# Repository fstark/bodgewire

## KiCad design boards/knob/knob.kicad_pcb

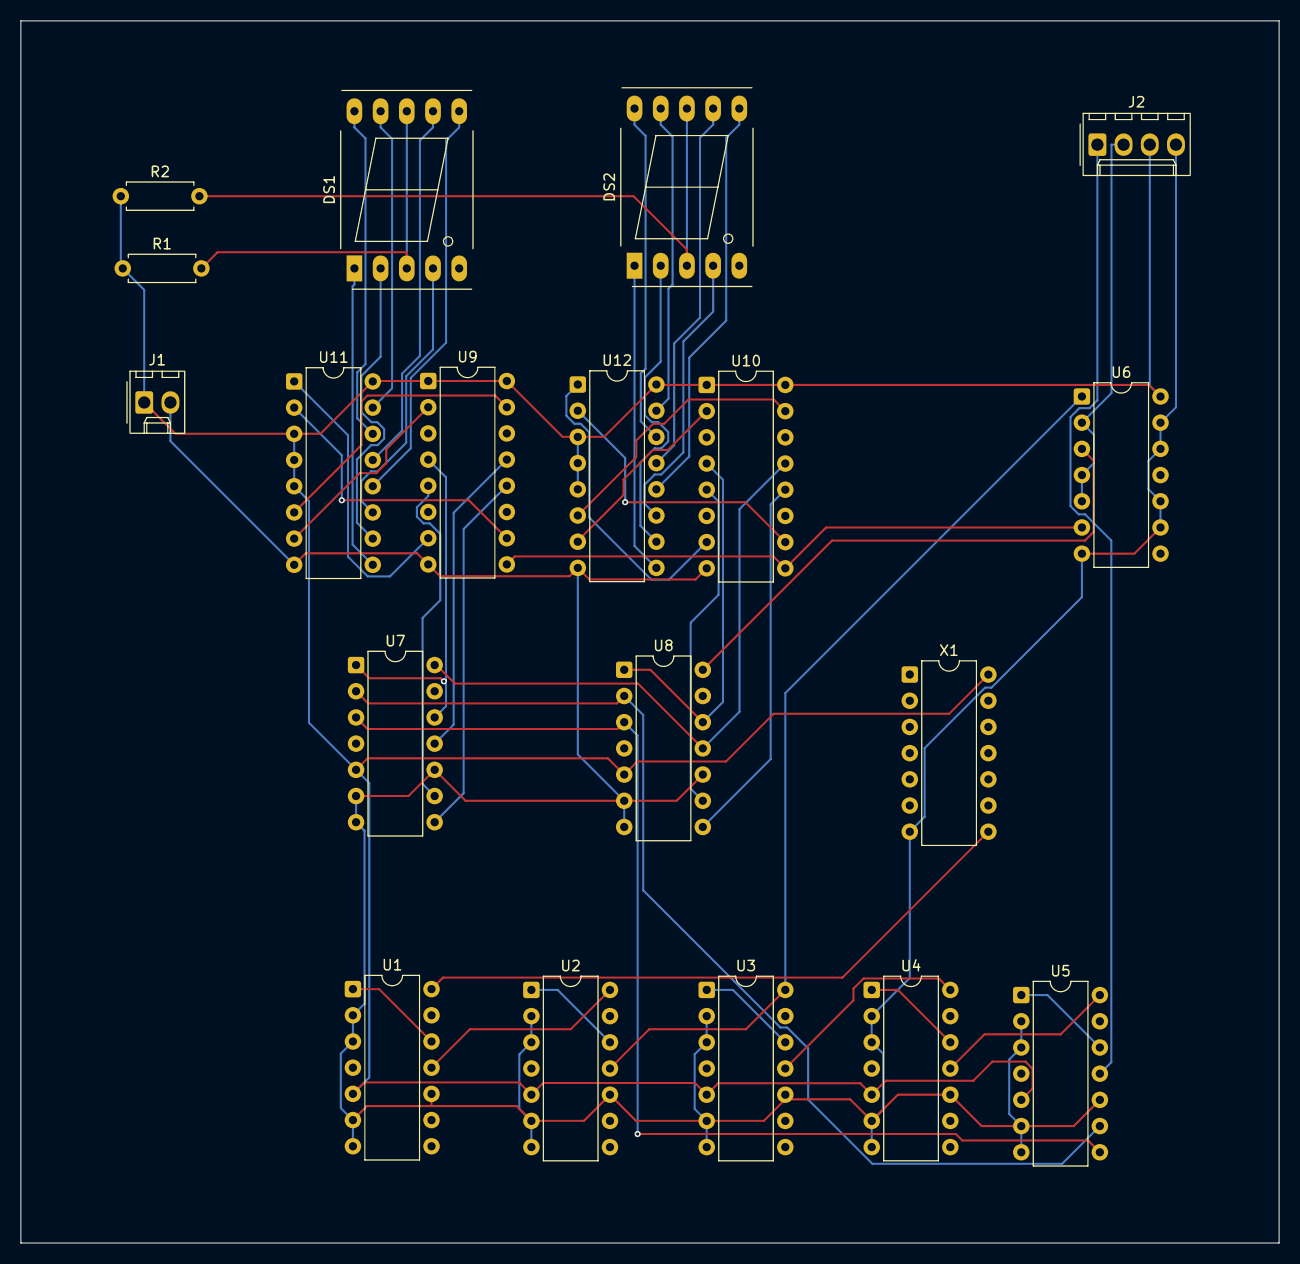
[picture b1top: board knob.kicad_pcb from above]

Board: 2 copper layers, 122.0 x 118.5 mm, 19 parts (0 on the bottom side), 50 nets.

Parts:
DS1, DS2: DIGIT; 7SegmentLED_LTS6760_LTS6780
J1: POWER; Molex_KK-254_AE-6410-02A_1x02_P2.54mm_Vertical
J2: PADDLE; Molex_KK-254_AE-6410-04A_1x04_P2.54mm_Vertical
R1, R2: 330; R_Axial_DIN0207_L6.3mm_D2.5mm_P7.62mm_Horizontal
U1, U2, U3, U4, U5, U7, U8: 74LS90; DIP-14_W7.62mm
U6: 74LS00; DIP-14_W7.62mm
U9, U10: 74LS175; DIP-16_W7.62mm
U11, U12: 74LS47; DIP-16_W7.62mm
X1: OSC; DIP-14_W7.62mm

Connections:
C0: U8.1 (CKB), U8.12 (QA), U10.4 (1D)
C1: U8.9 (QB), U10.5 (2D)
C2: U8.8 (QC), U10.12 (3D)
C3: U7.14 (CKA), U8.11 (QD), U10.13 (4D)
C4: U7.1 (CKB), U7.12 (QA), U9.4 (1D)
C5: U7.9 (QB), U9.5 (2D)
C6: U7.8 (QC), U9.12 (3D)
C7: U7.11 (QD), U9.13 (4D)
CLK: U1.14 (CKA), X1.8 (OUT)
DS1_A: DS1.7 (A), U11.13 (SA_N)
DS1_B: DS1.6 (B), U11.12 (SB_N)
DS1_C: DS1.4 (C), U11.11 (SC_N)
DS1_CA: DS1.3 (CA1), DS1.8 (CA2), R1.2
DS1_D: DS1.2 (D), U11.10 (SD_N)
DS1_E: DS1.1 (E), U11.9 (SE_N)
DS1_F: DS1.9 (F), U11.15 (SF_N)
DS1_G: DS1.10 (G), U11.14 (SG_N)
DS2_A: DS2.7 (A), U12.13 (SA_N)
DS2_B: DS2.6 (B), U12.12 (SB_N)
DS2_C: DS2.4 (C), U12.11 (SC_N)
DS2_CA: DS2.3 (CA1), DS2.8 (CA2), R2.2
DS2_D: DS2.2 (D), U12.10 (SD_N)
DS2_E: DS2.1 (E), U12.9 (SE_N)
DS2_F: DS2.9 (F), U12.15 (SF_N)
DS2_G: DS2.10 (G), U12.14 (SG_N)
F1K: U3.11 (QD), U4.14 (CKA)
F5K: U3.1 (CKB), U3.12 (QA)
F10K: U2.11 (QD), U3.14 (CKA), U6.1 (1A)
F50: U5.1 (CKB), U5.12 (QA)
F50K: U2.1 (CKB), U2.12 (QA)
F100: U4.11 (QD), U5.14 (CKA)
F100K: U1.11 (QD), U2.14 (CKA)
F500: U4.1 (CKB), U4.12 (QA)
F500K: U1.1 (CKB), U1.12 (QA)
GCLK: U6.3 (1Y), U8.14 (CKA)
GND: J1.2 (GND), J2.4 (GND), U1.2 (R01), U1.3 (R02), U1.6 (R91), U1.7 (R92), U1.10 (GND), U2.2 (R01), U2.3 (R02), U2.6 (R91), U2.7 (R92), U2.10 (GND), U3.2 (R01), U3.3 (R02), U3.6 (R91), U3.7 (R92), U3.10 (GND), U4.2 (R01), U4.3 (R02), U4.6 (R91), U4.7 (R92), U4.10 (GND), U5.2 (R01), U5.3 (R02), U5.6 (R91), U5.7 (R92), U5.10 (GND), U6.7 (GND), U6.9 (3A), U6.10 (3B), U6.12 (4A), U6.13 (4B), U7.6 (R91), U7.7 (R92), U7.10 (GND), U8.6 (R91), U8.7 (R92), U8.10 (GND), U9.8 (GND), U10.8 (GND), U11.8 (GND), U12.8 (GND), X1.7 (GND)
L0: U10.2 (1Q), U12.7 (A)
L1: U10.7 (2Q), U12.1 (B)
L2: U10.10 (3Q), U12.2 (C)
L3: U10.15 (4Q), U12.6 (D)
L4: U9.2 (1Q), U11.7 (A)
L5: U9.7 (2Q), U11.1 (B)
L6: U9.10 (3Q), U11.2 (C)
L7: U9.15 (4Q), U11.6 (D)
LATCH: U6.6 (2Y), U9.9 (CLK), U10.9 (CLK)
PULSE: J2.2 (OUT), U6.2 (1B), U6.4 (2A), U6.5 (2B)
TB1: U5.9 (QB), U7.2 (R01), U8.2 (R01)
TB2: U5.8 (QC), U7.3 (R02), U8.3 (R02)
TRIG_N: J2.1 (TRIG_N), U5.11 (QD)
VCC: J1.1 (VCC), J2.3 (VCC), R1.1, R2.1, U1.5 (VCC), U2.5 (VCC), U3.5 (VCC), U4.5 (VCC), U5.5 (VCC), U6.14 (VCC), U7.5 (VCC), U8.5 (VCC), U9.1 (CLR_N), U9.16 (VCC), U10.1 (CLR_N), U10.16 (VCC), U11.3 (LT_N), U11.4 (BI_N), U11.5 (RBI_N), U11.16 (VCC), U12.3 (LT_N), U12.4 (BI_N), U12.5 (RBI_N), U12.16 (VCC), X1.14 (VCC)

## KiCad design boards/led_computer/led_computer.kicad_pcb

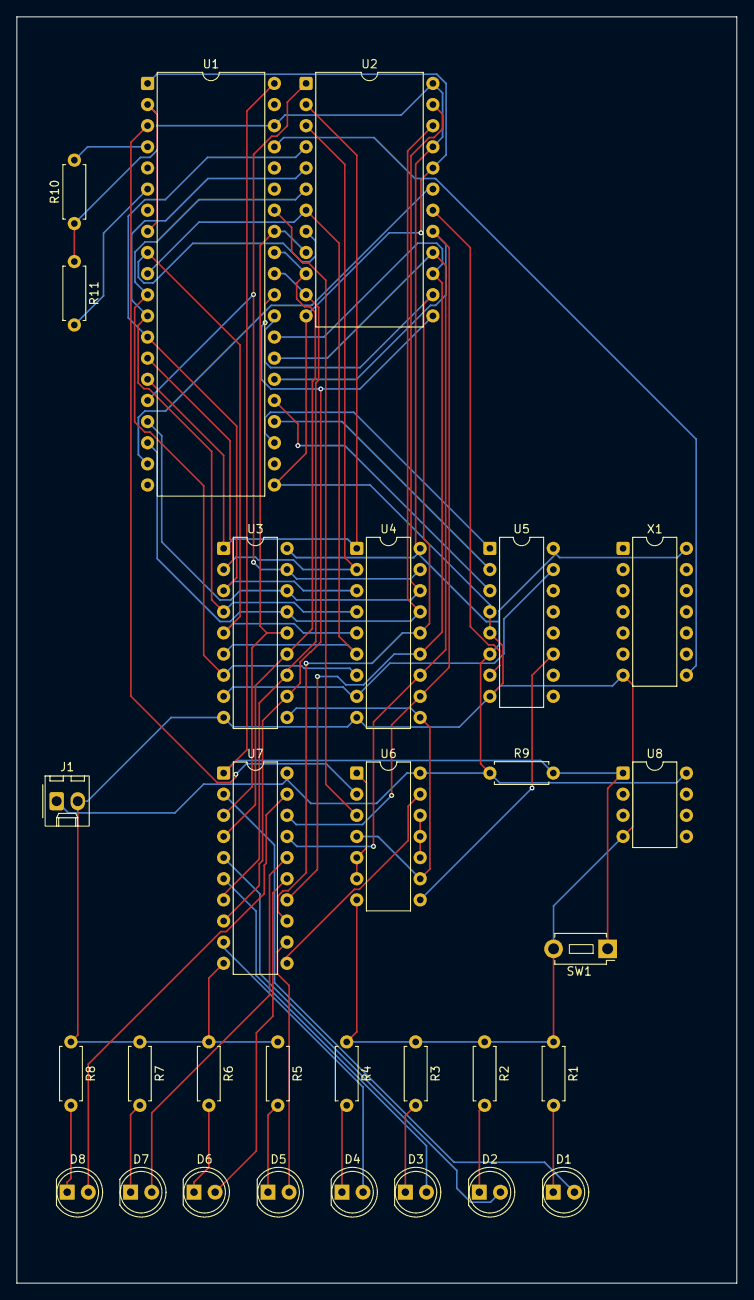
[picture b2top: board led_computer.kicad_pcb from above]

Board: 2 copper layers, 86.5 x 152.2 mm, 30 parts (0 on the bottom side), 53 nets.

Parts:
D1, D2, D3, D4, D5, D6, D7, D8: LED; LED_D5.0mm
J1: POWER; Molex_KK-254_AE-6410-02A_1x02_P2.54mm_Vertical
R1, R2, R3, R4, R5, R6, R7, R8: 330; R_Axial_DIN0207_L6.3mm_D2.5mm_P7.62mm_Horizontal
R9: 4k7; R_Axial_DIN0207_L6.3mm_D2.5mm_P7.62mm_Horizontal
R10, R11: 3k3; R_Axial_DIN0207_L6.3mm_D2.5mm_P7.62mm_Horizontal
SW1: BUTTON; SW_PUSH_1P1T_6x3.5mm_H5.0_APEM_MJTP1250
U1: 6502; DIP-40_W15.24mm
U2: 2716; DIP-24_W15.24mm
U3, U4: 2114; DIP-18_W7.62mm
U5: 74LS138; DIP-16_W7.62mm
U6: 74LS02; DIP-14_W7.62mm
U7: 74LS273; DIP-20_W7.62mm
U8: POR; DIP-8_W7.62mm
X1: OSC; DIP-14_W7.62mm

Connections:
A0: U1.9 (A0), U2.8 (A0), U3.5 (A0), U4.5 (A0)
A1: U1.10 (A1), U2.7 (A1), U3.6 (A1), U4.6 (A1)
A2: U1.11 (A2), U2.6 (A2), U3.7 (A2), U4.7 (A2)
A3: U1.12 (A3), U2.5 (A3), U3.4 (A3), U4.4 (A3)
A4: U1.13 (A4), U2.4 (A4), U3.3 (A4), U4.3 (A4)
A5: U1.14 (A5), U2.3 (A5), U3.2 (A5), U4.2 (A5)
A6: U1.15 (A6), U2.2 (A6), U3.1 (A6), U4.1 (A6)
A7: U1.16 (A7), U2.1 (A7), U3.17 (A7), U4.17 (A7)
A8: U1.17 (A8), U2.23 (A8), U3.16 (A8), U4.16 (A8)
A9: U1.18 (A9), U2.22 (A9), U3.15 (A9), U4.15 (A9)
A10: U1.19 (A10), U2.19 (A10)
A13: U1.23 (A13), U5.1 (A)
A14: U1.24 (A14), U5.2 (B)
A15: U1.25 (A15), U5.3 (C)
DB0: U1.33 (D0), U2.9 (O0), U3.14 (IO1), U7.3 (1D)
DB1: U1.32 (D1), U2.10 (O1), U3.13 (IO2), U7.4 (2D)
DB2: U1.31 (D2), U2.11 (O2), U3.12 (IO3), U7.7 (3D)
DB3: U1.30 (D3), U2.13 (O3), U3.11 (IO4), U7.8 (4D)
DB4: U1.29 (D4), U2.14 (O4), U4.14 (IO1), U7.13 (5D)
DB5: U1.28 (D5), U2.15 (O5), U4.13 (IO2), U7.14 (6D)
DB6: U1.27 (D6), U2.16 (O6), U4.12 (IO3), U7.17 (7D)
DB7: U1.26 (D7), U2.17 (O7), U4.11 (IO4), U7.18 (8D)
GND: J1.2 (GND), R1.1, R2.1, R3.1, R4.1, R5.1, R6.1, R7.1, R8.1, SW1.2, U1.1 (GND), U1.21 (GND2), U2.12 (GND), U2.20 (OE_N), U3.9 (GND), U4.9 (GND), U5.4 (G2A_N), U5.5 (G2B_N), U5.8 (GND), U6.7 (GND), U7.10 (GND), U8.4 (GND), X1.7 (GND)
IRQ_N: R10.2, U1.4 (IRQ_N)
L0: D1.2 (A), U7.2 (1Q)
L1: D2.2 (A), U7.5 (2Q)
L2: D3.2 (A), U7.6 (3Q)
L3: D4.2 (A), U7.9 (4Q)
L4: D5.2 (A), U7.12 (5Q)
L5: D6.2 (A), U7.15 (6Q)
L6: D7.2 (A), U7.16 (7Q)
L7: D8.2 (A), U7.19 (8Q)
LATCH_CLK: U6.13 (4Y), U7.11 (CLK)
LATCH_N: U5.11 (Y4_N), U6.8 (3A)
LATCH_WR: U6.10 (3Y), U6.11 (4A), U6.12 (4B)
LK0: D1.1 (K), R1.2
LK1: D2.1 (K), R2.2
LK2: D3.1 (K), R3.2
LK3: D4.1 (K), R4.2
LK4: D5.1 (K), R5.2
LK5: D6.1 (K), R6.2
LK6: D7.1 (K), R7.2
LK7: D8.1 (K), R8.2
NMI_N: R11.2, U1.6 (NMI_N)
PHI0: U1.37 (PHI0), X1.8 (OUT)
PHI1: U1.3 (PHI1), U6.2 (1A)
RAM_N: U3.8 (CS_N), U4.8 (CS_N), U5.15 (Y0_N)
RES_N: R9.2, SW1.1, U1.40 (RES_N), U7.1 (CLR_N), U8.1 (RST_N)
ROM_N: U2.18 (CE_N), U5.7 (Y7_N)
RW: U1.34 (RW), U6.3 (1B)
VCC: J1.1 (VCC), R9.1, R10.1, R11.1, U1.2 (RDY), U1.8 (VCC), U1.38 (SO), U2.21 (VPP), U2.24 (VCC), U3.18 (VCC), U4.18 (VCC), U5.6 (G1), U5.16 (VCC), U6.14 (VCC), U7.20 (VCC), U8.8 (VCC), X1.14 (VCC)
WR: U6.1 (1Y), U6.5 (2A), U6.6 (2B)
WR_N: U3.10 (WE_N), U4.10 (WE_N), U6.4 (2Y), U6.9 (3B)

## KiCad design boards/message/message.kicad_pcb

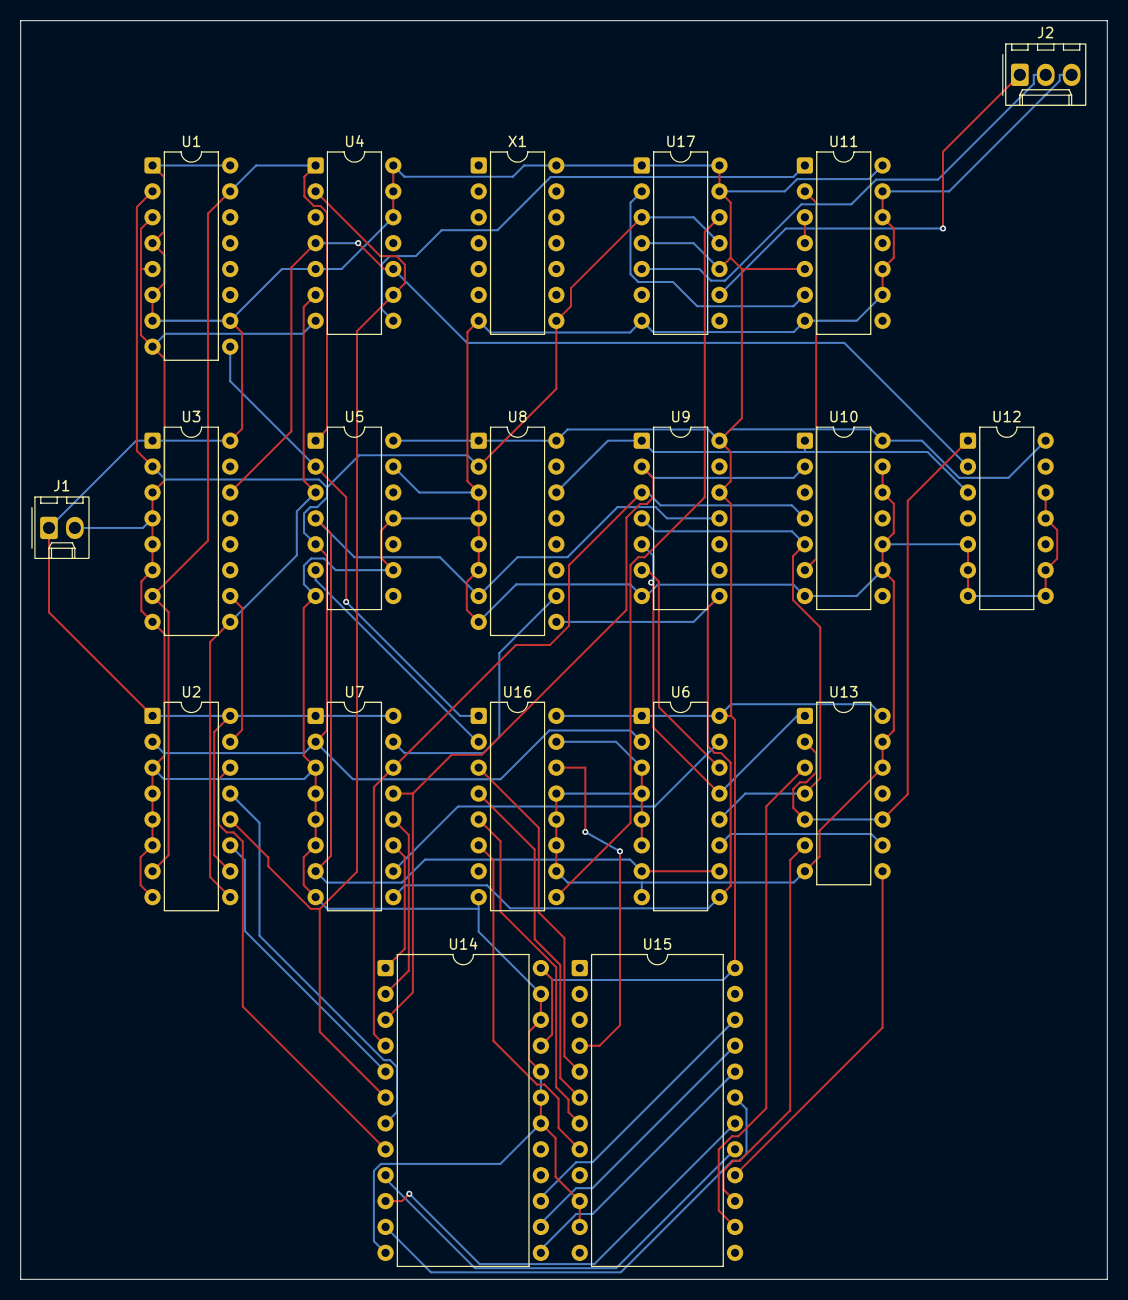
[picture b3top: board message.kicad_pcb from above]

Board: 2 copper layers, 106.6 x 123.5 mm, 20 parts (0 on the bottom side), 48 nets.

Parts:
J1: POWER; Molex_KK-254_AE-6410-02A_1x02_P2.54mm_Vertical
J2: VIDEO; Molex_KK-254_AE-6410-03A_1x03_P2.54mm_Vertical
U1, U2, U3, U6, U7, U8: 74LS161; DIP-16_W7.62mm
U4, U10: 74LS20; DIP-14_W7.62mm
U5: 74LS04; DIP-14_W7.62mm
U9: 74LS30; DIP-14_W7.62mm
U11: 74LS86; DIP-14_W7.62mm
U12: 74LS02; DIP-14_W7.62mm
U13: 74LS08; DIP-14_W7.62mm
U14: 2716; DIP-24_W15.24mm
U15: 2513; DIP-24_W15.24mm
U16: 74LS165; DIP-16_W7.62mm
U17: 74LS74; DIP-14_W7.62mm
X1: OSC; DIP-14_W7.62mm

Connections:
ACTIVE: U12.1 (1Y), U13.2 (1B), U13.5 (2B), U13.10 (3B)
C0: U2.14 (QA), U14.8 (A0)
C1: U2.13 (QB), U14.7 (A1)
C2: U2.12 (QC), U4.2 (1B), U4.9 (2A), U14.6 (A2)
C3: U2.11 (QD), U14.5 (A3)
C4: U3.14 (QA), U4.4 (1C), U4.10 (2B), U12.2 (1A)
CC: U2.15 (RCO), U3.10 (ENT)
CH0: U14.9 (O0), U15.17 (A4)
CH1: U14.10 (O1), U15.18 (A5)
CH2: U14.11 (O2), U15.19 (A6)
CH3: U14.13 (O3), U15.20 (A7)
CH4: U14.14 (O4), U15.21 (A8)
CH5: U14.15 (O5), U15.22 (A9)
CLK: U1.2 (CLK), U2.2 (CLK), U3.2 (CLK), U5.5 (3A), U6.2 (CLK), U7.2 (CLK), U8.2 (CLK), U17.3 (1CLK), U17.11 (2CLK), X1.8 (OUT)
CLK_N: U5.6 (3Y), U16.2 (CLK)
DOT_END: U1.15 (RCO), U2.7 (ENP), U3.7 (ENP), U4.1 (1A), U5.1 (1A)
DOT_LOAD_N: U1.9 (LOAD_N), U5.2 (1Y), U16.1 (SH_LD_N)
F1: U15.4 (O1), U16.14 (D)
F2: U15.5 (O2), U16.3 (E)
F3: U15.6 (O3), U16.4 (F)
F4: U15.7 (O4), U16.5 (G)
F5: U15.8 (O5), U16.6 (H)
FRAME_END_N: U6.9 (LOAD_N), U7.9 (LOAD_N), U8.9 (LOAD_N), U9.8 (Y)
GND: J1.2 (GND), J2.3 (GND), U1.3 (A), U1.5 (C), U1.8 (GND), U2.3 (A), U2.4 (B), U2.5 (C), U2.6 (D), U2.8 (GND), U3.3 (A), U3.4 (B), U3.5 (C), U3.6 (D), U3.8 (GND), U4.7 (GND), U5.7 (GND), U5.9 (4A), U5.11 (5A), U5.13 (6A), U6.3 (A), U6.4 (B), U6.5 (C), U6.6 (D), U6.8 (GND), U7.3 (A), U7.4 (B), U7.5 (C), U7.6 (D), U7.8 (GND), U8.3 (A), U8.4 (B), U8.5 (C), U8.6 (D), U8.8 (GND), U9.7 (GND), U10.7 (GND), U10.9 (2A), U10.10 (2B), U10.12 (2C), U10.13 (2D), U11.7 (GND), U11.9 (3A), U11.10 (3B), U11.12 (4A), U11.13 (4B), U12.5 (2A), U12.6 (2B), U12.7 (GND), U12.8 (3A), U12.9 (3B), U12.11 (4A), U12.12 (4B), U13.7 (GND), U13.12 (4A), U13.13 (4B), U14.12 (GND), U14.18 (CE_N), U14.19 (A10), U14.20 (OE_N), U14.22 (A9), U14.23 (A8), U15.10 (GND), U15.11 (CE_N), U16.8 (GND), U16.10 (SER), U16.11 (A), U16.12 (B), U16.13 (C), U16.15 (CLK_INH), U17.7 (GND), X1.7 (GND)
HSYNC_N: U4.8 (2Y), U11.1 (1A)
LINE_END: U5.4 (2Y), U6.7 (ENP), U6.10 (ENT), U7.7 (ENP), U8.7 (ENP), U9.11 (G)
LINE_END_N: U2.9 (LOAD_N), U3.9 (LOAD_N), U4.6 (1Y), U5.3 (2A)
R1: U13.3 (1Y), U15.14 (A1)
R2: U13.6 (2Y), U15.15 (A2)
R3: U13.8 (3Y), U15.16 (A3)
SYNC: U11.3 (1Y), U11.4 (2A)
SYNC_N: J2.2 (SYNC_N), U17.5 (1Q)
SYNC_N_D: U11.6 (2Y), U17.2 (1D)
V0: U6.14 (QA), U9.6 (F)
V1: U6.13 (QB), U9.5 (E), U13.1 (1A)
V2: U6.12 (QC), U9.4 (D), U10.5 (1D), U13.4 (2A)
V3: U6.11 (QD), U13.9 (3A)
V4: U7.14 (QA), U9.3 (C), U10.4 (1C), U14.4 (A4)
V5: U7.13 (QB), U9.2 (B), U10.2 (1B), U14.3 (A5)
V6: U7.12 (QC), U14.2 (A6)
V7: U7.11 (QD), U14.1 (A7)
V8: U8.14 (QA), U9.1 (A), U10.1 (1A), U12.3 (1B)
VC1: U6.15 (RCO), U7.10 (ENT)
VC2: U7.15 (RCO), U8.10 (ENT)
VCC: J1.1 (VCC), U1.1 (CLR_N), U1.4 (B), U1.6 (D), U1.7 (ENP), U1.10 (ENT), U1.16 (VCC), U2.1 (CLR_N), U2.10 (ENT), U2.16 (VCC), U3.1 (CLR_N), U3.16 (VCC), U4.5 (1D), U4.12 (2C), U4.13 (2D), U4.14 (VCC), U5.14 (VCC), U6.1 (CLR_N), U6.16 (VCC), U7.1 (CLR_N), U7.16 (VCC), U8.1 (CLR_N), U8.16 (VCC), U9.12 (H), U9.14 (VCC), U10.14 (VCC), U11.5 (2B), U11.14 (VCC), U12.14 (VCC), U13.14 (VCC), U14.21 (VPP), U14.24 (VCC), U15.24 (VCC), U16.16 (VCC), U17.1 (1CLR_N), U17.4 (1PRE_N), U17.10 (2PRE_N), U17.13 (2CLR_N), U17.14 (VCC), X1.14 (VCC)
VIDEO: J2.1 (VIDEO), U17.9 (2Q)
VIDEO_D: U16.9 (QH), U17.12 (2D)
VSYNC_N: U10.6 (1Y), U11.2 (1B)

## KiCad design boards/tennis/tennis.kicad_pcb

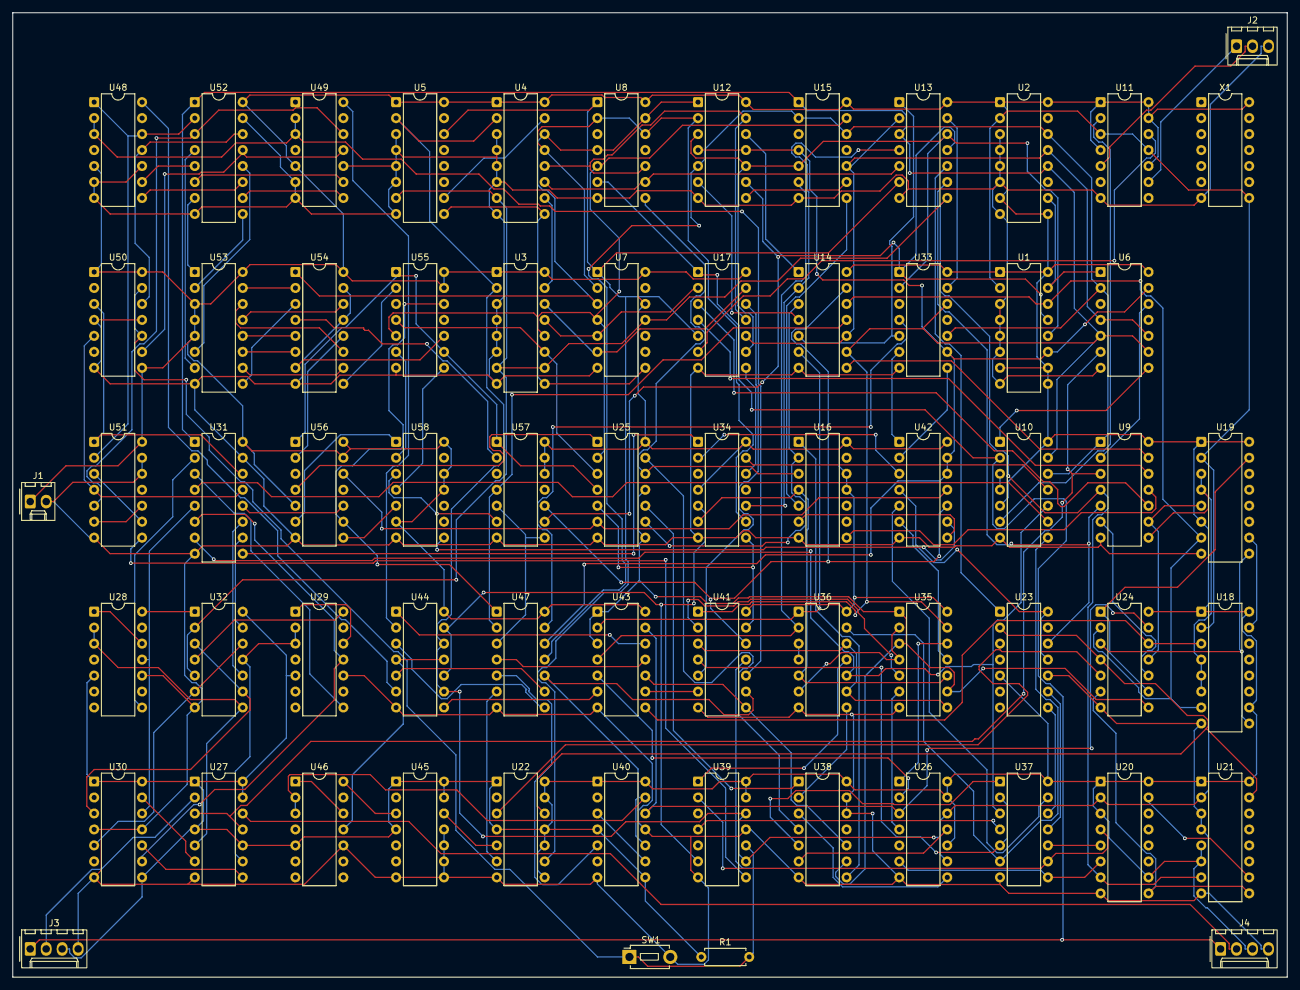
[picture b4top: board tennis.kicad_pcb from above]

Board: 2 copper layers, 202.6 x 153.3 mm, 65 parts (0 on the bottom side), 182 nets.

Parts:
J1: POWER; Molex_KK-254_AE-6410-02A_1x02_P2.54mm_Vertical
J2: VIDEO; Molex_KK-254_AE-6410-03A_1x03_P2.54mm_Vertical
J3, J4: PADDLE; Molex_KK-254_AE-6410-04A_1x04_P2.54mm_Vertical
R1: 1k; R_Axial_DIN0207_L6.3mm_D2.5mm_P7.62mm_Horizontal
SW1: BUTTON; SW_PUSH_1P1T_6x3.5mm_H5.0_APEM_MJTP1250
U1, U2, U3, U4, U5, U18, U19, U20, U21: 74LS161; DIP-16_W7.62mm
U6, U8, U15, U33, U34, U55, U56, U57: 74LS20; DIP-14_W7.62mm
U7, U16, U58: 74LS30; DIP-14_W7.62mm
U9, U41: 74LS04; DIP-14_W7.62mm
U10: 74LS86; DIP-14_W7.62mm
U11, U27: 74LS74; DIP-14_W7.62mm
U12, U17, U35, U43: 74LS27; DIP-14_W7.62mm
U13, U25, U32, U37, U47: 74LS02; DIP-14_W7.62mm
U14, U24, U42, U51: 74LS00; DIP-14_W7.62mm
U22, U26, U30, U39, U40, U44, U45, U50: 74LS107; DIP-14_W7.62mm
U23, U28, U29, U46: 74LS93; DIP-14_W7.62mm
U31, U52, U54: 74LS157; DIP-16_W7.62mm
U36: 74LS08; DIP-14_W7.62mm
U38: 74LS32; DIP-14_W7.62mm
U48, U49: 74LS90; DIP-14_W7.62mm
U53: 74LS48; DIP-16_W7.62mm
X1: OSC; DIP-14_W7.62mm

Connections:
A_TOP: U54.12 (4Y), U56.2 (1B)
BALLV_N: U16.1 (A), U38.8 (3Y)
BALL_CK: U13.10 (3Y), U23.1 (CKB)
BALL_N: U24.8 (3Y), U25.8 (3A), U25.11 (4A), U35.1 (1A), U35.3 (2A), U35.9 (3A), U38.9 (3A), U43.1 (1A), U43.3 (2A)
BALL_OFF: U9.5 (3A), U13.9 (3B), U23.12 (QA)
BALL_QB: U23.9 (QB), U37.11 (4A)
BALL_QC: U23.8 (QC), U37.12 (4B)
BALL_QD: U23.11 (QD), U23.14 (CKA), U42.4 (2A)
BC: U54.7 (2Y), U55.10 (2B)
BHC: U18.15 (RCO), U19.10 (ENT)
BOTTOM_N: U8.8 (2Y), U16.3 (C), U25.12 (4B)
BV8: U22.3 (1Q), U23.3 (R02), U24.5 (2B)
BVC: U20.15 (RCO), U21.10 (ENT)
CLK: U1.2 (CLK), U2.2 (CLK), U3.2 (CLK), U4.2 (CLK), U5.2 (CLK), U11.3 (1CLK), U11.11 (2CLK), U18.2 (CLK), U19.2 (CLK), U20.2 (CLK), U21.2 (CLK), U26.9 (2CLK), U26.12 (1CLK), U39.9 (2CLK), U39.12 (1CLK), U44.9 (2CLK), U44.12 (1CLK), X1.8 (OUT)
COL3: U47.1 (1Y), U55.12 (2C), U56.9 (2A)
COL_L_N: U33.6 (1Y), U42.1 (1A)
COL_R_N: U33.8 (2Y), U42.2 (1B)
FAST: U40.5 (2Q), U47.5 (2A)
FE: U54.4 (1Y), U57.2 (1B)
FRAME0: U22.5 (2Q), U45.12 (1CLK)
FRAME0_N: U22.6 (2Q_N), U47.6 (2B)
FRAME1: U45.3 (1Q), U46.14 (CKA)
FRAME_END_N: U3.9 (LOAD_N), U4.9 (LOAD_N), U5.9 (LOAD_N), U7.8 (Y)
GD: U54.9 (3Y), U55.2 (1B)
GLYPH: U42.9 (3A), U58.8 (Y)
GND: J1.2 (GND), J2.3 (GND), J3.4 (GND), J4.4 (GND), SW1.2, U1.3 (A), U1.4 (B), U1.5 (C), U1.6 (D), U1.8 (GND), U2.3 (A), U2.4 (B), U2.5 (C), U2.6 (D), U2.8 (GND), U3.3 (A), U3.4 (B), U3.5 (C), U3.6 (D), U3.8 (GND), U4.3 (A), U4.4 (B), U4.5 (C), U4.6 (D), U4.8 (GND), U5.3 (A), U5.4 (B), U5.5 (C), U5.6 (D), U5.8 (GND), U6.7 (GND), U7.7 (GND), U8.7 (GND), U9.7 (GND), U10.7 (GND), U11.7 (GND), U12.7 (GND), U13.7 (GND), U14.7 (GND), U15.7 (GND), U16.7 (GND), U17.7 (GND), U18.8 (GND), U19.8 (GND), U20.8 (GND), U21.3 (A), U21.4 (B), U21.8 (GND), U22.7 (GND), U23.10 (GND), U24.7 (GND), U25.7 (GND), U26.7 (GND), U27.7 (GND), U28.10 (GND), U29.10 (GND), U30.4 (1K), U30.7 (GND), U30.11 (2K), U31.8 (GND), U31.15 (G_N), U32.7 (GND), U33.7 (GND), U34.7 (GND), U35.7 (GND), U36.7 (GND), U37.7 (GND), U38.7 (GND), U38.12 (4A), U38.13 (4B), U39.7 (GND), U39.11 (2K), U40.7 (GND), U40.11 (2K), U41.7 (GND), U42.7 (GND), U43.7 (GND), U44.7 (GND), U45.7 (GND), U45.8 (2J), U45.9 (2CLK), U45.10 (2CLR_N), U45.11 (2K), U46.10 (GND), U47.7 (GND), U48.6 (R91), U48.7 (R92), U48.10 (GND), U49.6 (R91), U49.7 (R92), U49.10 (GND), U50.4 (1K), U50.7 (GND), U50.11 (2K), U51.7 (GND), U51.12 (4A), U51.13 (4B), U52.8 (GND), U52.15 (G_N), U53.8 (GND), U54.8 (GND), U54.13 (4B), U54.15 (G_N), U55.7 (GND), U56.7 (GND), U57.7 (GND), U58.7 (GND), X1.7 (GND)
GO_DOWN: U26.8 (2J), U38.3 (1Y)
GO_LEFT: U26.4 (1K), U35.6 (2Y)
GO_RIGHT: U26.1 (1J), U35.12 (1Y)
GO_UP: U26.11 (2K), U38.6 (2Y)
H0: U1.14 (QA), U14.12 (4A), U18.7 (ENP), U19.7 (ENP), U24.2 (1B)
H1: U1.13 (QB), U12.9 (3A), U13.11 (4A), U33.1 (1A), U57.9 (2A)
H2: U1.12 (QC), U12.3 (2A), U12.10 (3B), U13.12 (4B), U15.5 (1D), U17.9 (3A), U33.2 (1B)
H3: U1.11 (QD), U6.13 (2D), U12.4 (2B), U12.11 (3C), U15.4 (1C), U33.9 (2A), U42.12 (4A), U42.13 (4B), U47.12 (4B)
H3_N: U25.6 (2B), U42.11 (4Y), U56.12 (2C)
H4: U2.14 (QA), U6.2 (1B), U9.1 (1A), U10.12 (4A), U12.5 (2C), U15.2 (1B), U15.12 (2C), U33.10 (2B), U47.11 (4A)
H4_N: U6.12 (2C), U9.2 (1Y)
H5: U2.13 (QB), U6.4 (1C), U6.10 (2B), U13.2 (1A), U14.10 (3B), U15.10 (2B), U17.10 (3B)
H6: U2.12 (QC), U6.5 (1D), U6.9 (2A), U10.13 (4B), U13.3 (1B), U14.9 (3A), U15.1 (1A), U31.1 (S), U33.12 (2C), U35.13 (1C), U41.1 (1A), U52.1 (S)
H6_N: U35.5 (2C), U41.2 (1Y)
H12_LOW: U13.13 (4Y), U33.13 (2D)
H34_LOW: U33.4 (1C), U47.13 (4Y)
H56_LOW: U13.1 (1Y), U14.5 (2B), U33.5 (1D)
HBALL: U19.15 (RCO), U24.1 (1A), U24.9 (3A)
HBLANK: U9.12 (6Y), U17.4 (2B)
HBLANK_N: U9.13 (6A), U14.8 (3Y)
HC: U1.15 (RCO), U2.10 (ENT), U6.1 (1A)
HDIR: U24.13 (4B), U26.3 (1Q), U40.12 (1CLK), U43.13 (1C)
HDIR_N: U26.2 (1Q_N), U43.5 (2C)
HIT_BOTTOM: U25.13 (4Y), U38.4 (2A)
HIT_HIGH: U37.1 (1Y), U38.5 (2B)
HIT_LOW: U36.8 (3Y), U38.2 (1B)
HIT_TOP: U25.10 (3Y), U38.1 (1A)
HLOAD_N: U18.9 (LOAD_N), U19.9 (LOAD_N), U24.3 (1Y)
HMOVE: U18.3 (A), U24.12 (4A), U43.8 (3Y)
HSYNC_N: U6.8 (2Y), U10.1 (1A)
HX: U10.11 (4Y), U34.13 (2D)
LDONE: U30.3 (1Q), U32.3 (1B), U32.9 (3B)
LEFT_A: U12.6 (2Y), U14.4 (2A)
LEFT_N: U14.6 (2Y), U36.1 (1A), U43.2 (1B)
LINE_END: U3.7 (ENP), U3.10 (ENT), U4.7 (ENP), U5.7 (ENP), U7.11 (G), U9.4 (2Y), U13.8 (3A), U20.7 (ENP), U21.7 (ENP), U32.2 (1A), U32.5 (2A)
LINE_END_N: U6.6 (1Y), U9.3 (2A), U27.3 (1CLK), U27.11 (2CLK)
LOST_LEFT: U44.3 (1Q), U47.8 (3A)
LOST_LEFT_N: U44.2 (1Q_N), U49.14 (CKA)
LOST_RIGHT: U44.5 (2Q), U47.9 (3B)
LOST_RIGHT_N: U44.6 (2Q_N), U48.14 (CKA)
LP0: U28.1 (CKB), U28.12 (QA)
LP2: U28.8 (QC), U31.2 (1A)
LP3: U28.11 (QD), U30.12 (1CLK), U31.5 (2A)
LPADV: U31.11 (3A), U32.10 (3Y)
LPAD_CK: U28.14 (CKA), U32.1 (1Y)
LPULSE: J3.2 (OUT), U27.2 (1D)
LWAIT: U27.5 (1Q), U28.2 (R01), U28.3 (R02), U32.8 (3A)
LWAIT_N: U27.6 (1Q_N), U30.13 (1CLR_N)
MID_A: U37.13 (4Y), U42.5 (2B)
MID_N: U35.11 (3C), U42.6 (2Y)
MISS_LEFT: U43.12 (1Y), U44.1 (1J)
MISS_RIGHT: U43.6 (2Y), U44.8 (2J)
MIX: U9.11 (5A), U16.8 (Y)
MIX_N: U9.10 (5Y), U17.3 (2A)
MOVE: U17.12 (1Y), U41.5 (3A)
MOVE_N: U41.6 (3Y), U43.9 (3A)
MR: U9.8 (4Y), U18.4 (B), U18.5 (C), U18.6 (D), U19.3 (A), U19.4 (B)
MR_N: U9.9 (4A), U19.5 (C), U24.11 (4Y)
NET_A: U12.8 (3Y), U15.9 (2A)
NET_N: U15.8 (2Y), U16.5 (E)
PADV: U31.9 (3Y), U34.1 (1A)
PAD_HIT: U35.8 (3Y), U36.9 (3A), U36.12 (4A), U41.3 (2A)
PAD_HIT_N: U37.2 (1A), U37.5 (2A), U41.4 (2Y)
PAD_N: U16.4 (D), U34.6 (1Y), U35.10 (3B), U36.5 (2B)
PCOL: U34.2 (1B), U42.3 (1Y)
PLAY: U34.5 (1D), U39.6 (2Q_N), U44.10 (2CLR_N), U44.13 (1CLR_N)
QH0_N: U14.11 (4Y), U47.2 (1A), U57.4 (1C)
QH1_N: U47.3 (1B), U57.5 (1D), U57.8 (2Y)
RDONE: U30.5 (2Q), U32.6 (2B), U32.12 (4B)
REGION: U14.13 (4B), U41.12 (6Y), U42.10 (3B), U57.10 (2B)
REGION_N: U25.5 (2A), U34.8 (2Y), U41.13 (6A)
RIGHT_N: U15.6 (1Y), U36.2 (1B), U43.4 (2B)
RP0: U29.1 (CKB), U29.12 (QA)
RP2: U29.8 (QC), U31.3 (1B)
RP3: U29.11 (QD), U30.9 (2CLK), U31.6 (2B)
RPADV: U31.10 (3B), U32.13 (4Y)
RPAD_CK: U29.14 (CKA), U32.4 (2Y)
RPULSE: J4.2 (OUT), U27.12 (2D)
RWAIT: U27.9 (2Q), U29.2 (R01), U29.3 (R02), U32.11 (4A)
RWAIT_N: U27.8 (2Q_N), U30.10 (2CLR_N)
SC0: U52.4 (1Y), U53.7 (A)
SC1: U52.7 (2Y), U53.1 (B)
SC2: U52.9 (3Y), U53.2 (C)
SC3: U52.12 (4Y), U53.6 (D)
SCORE_A: U17.8 (3Y), U34.12 (2C)
SCORE_N: U16.6 (F), U42.8 (3Y)
SEG_A: U53.13 (SA), U54.14 (4A)
SEG_B: U53.12 (SB), U54.5 (2A)
SEG_C: U53.11 (SC), U54.6 (2B)
SEG_D: U53.10 (SD), U54.10 (3B)
SEG_E: U53.9 (SE), U54.3 (1B)
SEG_F: U53.15 (SF), U54.2 (1A)
SEG_G: U53.14 (SG), U54.11 (3A)
SERVE_END: U44.4 (1K), U44.11 (2K), U46.11 (QD)
SERVING: U38.10 (3B), U41.8 (4Y), U43.10 (3B)
SERVING_N: U40.10 (2CLR_N), U40.13 (1CLR_N), U41.9 (4A), U46.2 (R01), U46.3 (R02), U47.10 (3Y)
SET_SHALLOW: U36.11 (4Y), U39.1 (1J)
SET_STEEP: U37.4 (2Y), U39.4 (1K)
SIDES_N: U36.3 (1Y), U36.4 (2A)
SKIP: U43.11 (3C), U47.4 (2Y)
SL0: U48.1 (CKB), U48.12 (QA), U51.2 (1B), U52.2 (1A)
SL1: U48.9 (QB), U52.5 (2A)
SL2: U48.8 (QC), U52.11 (3A)
SL3: U48.11 (QD), U50.12 (1CLK), U52.14 (4A)
SP2: U10.9 (3A), U31.4 (1Y)
SP3: U10.10 (3B), U31.7 (2Y), U36.10 (3B), U37.3 (1B)
SP_MID: U10.8 (3Y), U36.13 (4B), U37.6 (2B)
SR0: U49.1 (CKB), U49.12 (QA), U51.5 (2B), U52.3 (1B)
SR1: U49.9 (QB), U52.6 (2B)
SR2: U49.8 (QC), U52.10 (3B)
SR3: U49.11 (QD), U50.9 (2CLK), U52.13 (4B)
ST0: U46.1 (CKB), U46.12 (QA)
START: U41.10 (5Y), U48.2 (R01), U48.3 (R02), U49.2 (R01), U49.3 (R02)
START_N: R1.2, SW1.1, U39.10 (2CLR_N), U41.11 (5A), U50.10 (2CLR_N), U50.13 (1CLR_N)
STEEP: U20.4 (B), U37.9 (3B), U39.2 (1Q_N)
SYNC: U10.3 (1Y), U10.4 (2A)
SYNC_N: J2.2 (SYNC_N), U11.5 (1Q)
SYNC_N_D: U10.6 (2Y), U11.2 (1D)
T1_N: U56.6 (1Y), U58.1 (A)
T2_N: U55.6 (1Y), U58.2 (B)
T3_N: U57.6 (1Y), U58.3 (C)
T4_N: U55.8 (2Y), U58.4 (D)
T5_N: U56.8 (2Y), U58.5 (E)
TENS: U31.12 (4Y), U56.10 (2B)
TENS_L: U31.14 (4A), U50.3 (1Q), U51.1 (1A)
TENS_R: U31.13 (4B), U50.5 (2Q), U51.4 (2A)
TOP_A: U12.12 (1Y), U14.1 (1A)
TOP_B: U13.4 (2Y), U14.2 (1B), U34.10 (2B)
TOP_N: U14.3 (1Y), U16.2 (B), U25.9 (3B)
TURN_N: U35.2 (1B), U35.4 (2B), U36.6 (2Y)
TURN_ODD: U40.3 (1Q), U40.9 (2CLK)
UNITS: U25.4 (2Y), U55.1 (1A), U55.9 (2A), U56.1 (1A), U57.1 (1A)
V0: U3.14 (QA), U7.6 (F), U17.13 (1C)
V1: U3.13 (QB), U7.5 (E), U17.2 (1B)
V2: U3.12 (QC), U7.4 (D), U8.5 (1D), U15.13 (2D), U25.2 (1A), U55.5 (1D)
V3: U3.11 (QD), U25.3 (1B), U55.4 (1C)
V4: U4.14 (QA), U7.3 (C), U8.4 (1C), U8.13 (2D), U12.1 (1A), U54.1 (S)
V5: U4.13 (QB), U7.2 (B), U8.2 (1B), U8.12 (2C), U12.2 (1B), U34.9 (2A)
V6: U4.12 (QC), U8.10 (2B), U12.13 (1C), U17.11 (3C)
V7: U4.11 (QD), U8.9 (2A), U13.5 (2A)
V8: U5.14 (QA), U7.1 (A), U8.1 (1A), U13.6 (2B), U17.5 (2C), U22.9 (2CLK)
V23_LOW: U25.1 (1Y), U56.4 (1C)
VBALL: U9.6 (3Y), U24.10 (3B)
VC1: U3.15 (RCO), U4.10 (ENT)
VC2: U4.15 (RCO), U5.10 (ENT)
VCC: J1.1 (VCC), J3.3 (VCC), J4.3 (VCC), R1.1, U1.1 (CLR_N), U1.7 (ENP), U1.9 (LOAD_N), U1.10 (ENT), U1.16 (VCC), U2.1 (CLR_N), U2.7 (ENP), U2.9 (LOAD_N), U2.16 (VCC), U3.1 (CLR_N), U3.16 (VCC), U4.1 (CLR_N), U4.16 (VCC), U5.1 (CLR_N), U5.16 (VCC), U6.14 (VCC), U7.12 (H), U7.14 (VCC), U8.14 (VCC), U9.14 (VCC), U10.5 (2B), U10.14 (VCC), U11.1 (1CLR_N), U11.4 (1PRE_N), U11.10 (2PRE_N), U11.13 (2CLR_N), U11.14 (VCC), U12.14 (VCC), U13.14 (VCC), U14.14 (VCC), U15.14 (VCC), U16.11 (G), U16.12 (H), U16.14 (VCC), U17.14 (VCC), U18.1 (CLR_N), U18.10 (ENT), U18.16 (VCC), U19.1 (CLR_N), U19.6 (D), U19.16 (VCC), U20.1 (CLR_N), U20.3 (A), U20.10 (ENT), U20.16 (VCC), U21.1 (CLR_N), U21.5 (C), U21.6 (D), U21.16 (VCC), U22.1 (1J), U22.4 (1K), U22.8 (2J), U22.10 (2CLR_N), U22.11 (2K), U22.13 (1CLR_N), U22.14 (VCC), U23.5 (VCC), U24.14 (VCC), U25.14 (VCC), U26.10 (2CLR_N), U26.13 (1CLR_N), U26.14 (VCC), U27.1 (1CLR_N), U27.4 (1PRE_N), U27.10 (2PRE_N), U27.13 (2CLR_N), U27.14 (VCC), U28.5 (VCC), U29.5 (VCC), U30.1 (1J), U30.8 (2J), U30.14 (VCC), U31.16 (VCC), U32.14 (VCC), U33.14 (VCC), U34.4 (1C), U34.14 (VCC), U35.14 (VCC), U36.14 (VCC), U37.14 (VCC), U38.14 (VCC), U39.13 (1CLR_N), U39.14 (VCC), U40.1 (1J), U40.4 (1K), U40.8 (2J), U40.14 (VCC), U41.14 (VCC), U42.14 (VCC), U43.14 (VCC), U44.14 (VCC), U45.1 (1J), U45.4 (1K), U45.13 (1CLR_N), U45.14 (VCC), U46.5 (VCC), U47.14 (VCC), U48.5 (VCC), U49.5 (VCC), U50.1 (1J), U50.8 (2J), U50.14 (VCC), U51.14 (VCC), U52.16 (VCC), U53.3 (LT_N), U53.4 (BI_N), U53.5 (RBI_N), U53.16 (VCC), U54.16 (VCC), U55.13 (2D), U55.14 (VCC), U56.5 (1D), U56.13 (2D), U56.14 (VCC), U57.12 (2C), U57.13 (2D), U57.14 (VCC), U58.6 (F), U58.11 (G), U58.12 (H), U58.14 (VCC), X1.14 (VCC)
VDIR_N: U20.6 (D), U26.6 (2Q_N), U37.8 (3A)
VIDEO: J2.1 (VIDEO), U11.9 (2Q)
VIDEO_D: U11.12 (2D), U17.6 (2Y)
VLOAD_C: U20.5 (C), U37.10 (3Y)
VLOAD_N: U20.9 (LOAD_N), U21.9 (LOAD_N), U24.6 (2Y)
VRCO: U21.15 (RCO), U22.12 (1CLK), U23.2 (R01), U24.4 (2A)
VSYNC_N: J3.1 (TRIG_N), J4.1 (TRIG_N), U8.6 (1Y), U10.2 (1B), U17.1 (1A)
WIN: U39.8 (2J), U51.8 (3Y)
WIN_L_N: U51.3 (1Y), U51.9 (3A)
WIN_R_N: U51.6 (2Y), U51.10 (3B)

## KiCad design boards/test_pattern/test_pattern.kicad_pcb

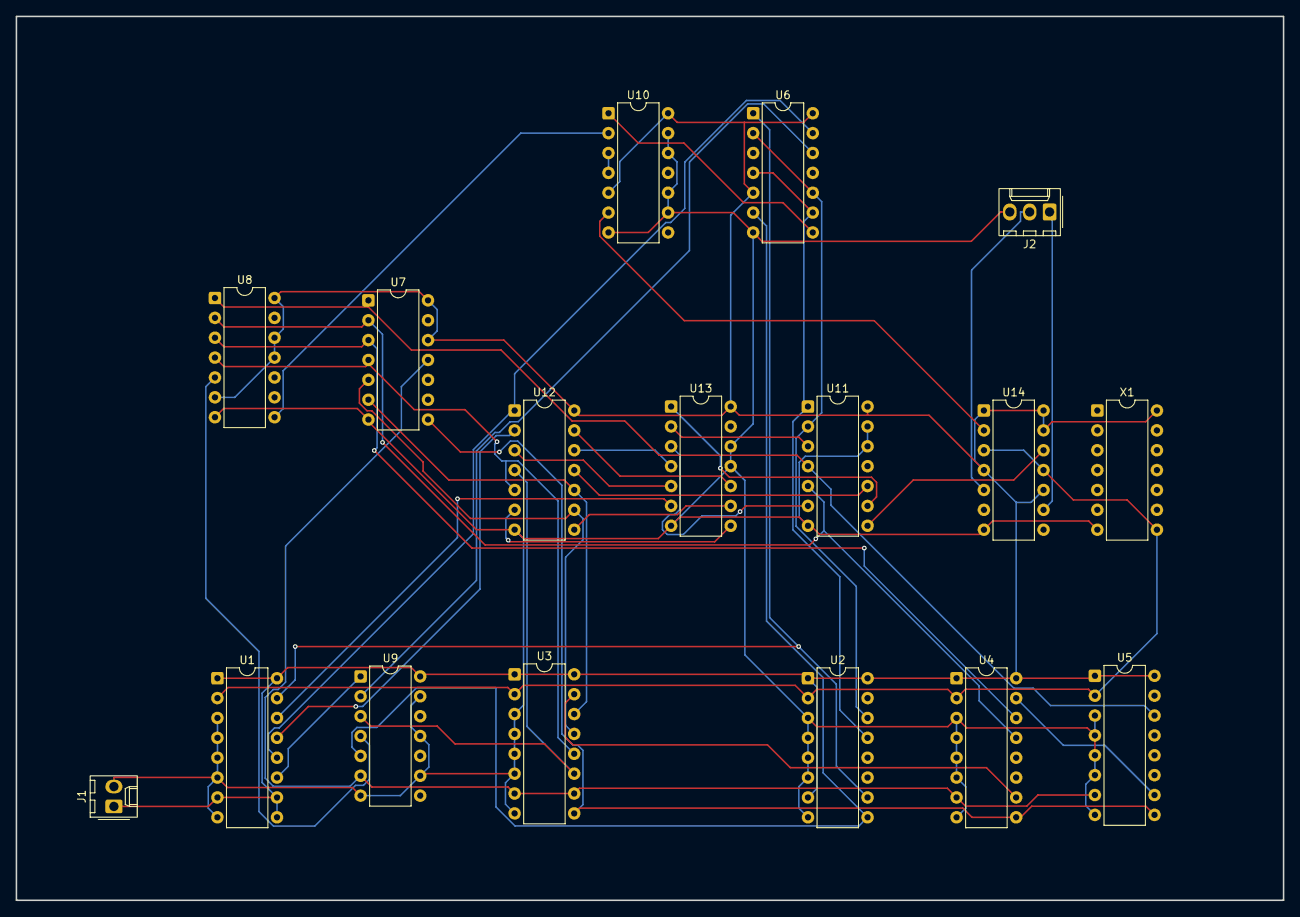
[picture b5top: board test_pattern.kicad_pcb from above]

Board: 2 copper layers, 162.0 x 113.0 mm, 17 parts (0 on the bottom side), 40 nets.

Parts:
J1: POWER; Molex_KK-254_AE-6410-02A_1x02_P2.54mm_Vertical
J2: VIDEO; Molex_KK-254_AE-6410-03A_1x03_P2.54mm_Vertical
U1, U2, U3, U4, U5: 74LS161; DIP-16_W7.62mm
U6: 74LS20; DIP-14_W7.62mm
U7, U8: 74LS30; DIP-14_W7.62mm
U9: 74LS04; DIP-14_W7.62mm
U10: 74LS86; DIP-14_W7.62mm
U11: 74LS08; DIP-14_W7.62mm
U12: 74LS32; DIP-14_W7.62mm
U13: 74LS02; DIP-14_W7.62mm
U14: 74LS74; DIP-14_W7.62mm
X1: OSC; DIP-14_W7.62mm

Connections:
ACTIVE: U11.9 (3A), U13.1 (1Y)
CLK: U1.2 (CLK), U2.2 (CLK), U3.2 (CLK), U4.2 (CLK), U5.2 (CLK), U14.3 (1CLK), U14.11 (2CLK), X1.8 (OUT)
FRAME_END_N: U3.9 (LOAD_N), U4.9 (LOAD_N), U5.9 (LOAD_N), U7.8 (Y)
GND: J1.2 (GND), J2.3 (GND), U1.3 (A), U1.4 (B), U1.5 (C), U1.6 (D), U1.8 (GND), U2.3 (A), U2.4 (B), U2.5 (C), U2.6 (D), U2.8 (GND), U3.3 (A), U3.4 (B), U3.5 (C), U3.6 (D), U3.8 (GND), U4.3 (A), U4.4 (B), U4.5 (C), U4.6 (D), U4.8 (GND), U5.3 (A), U5.4 (B), U5.5 (C), U5.6 (D), U5.8 (GND), U6.7 (GND), U7.7 (GND), U8.7 (GND), U9.7 (GND), U9.9 (4A), U9.11 (5A), U9.13 (6A), U10.7 (GND), U10.9 (3A), U10.10 (3B), U10.12 (4A), U10.13 (4B), U11.7 (GND), U11.12 (4A), U11.13 (4B), U12.7 (GND), U13.7 (GND), U13.11 (4A), U13.12 (4B), U14.7 (GND), X1.7 (GND)
GRID: U11.10 (3B), U12.11 (4Y)
GRIDH: U12.12 (4A), U13.4 (2Y)
GRIDV: U12.13 (4B), U13.10 (3Y)
H0: U1.14 (QA), U13.6 (2B)
H1: U1.13 (QB), U12.2 (1B)
H2: U1.12 (QC), U6.13 (2D), U12.1 (1A)
H3: U1.11 (QD), U9.1 (1A)
H3_N: U6.12 (2C), U9.2 (1Y)
H4: U2.14 (QA), U6.2 (1B), U6.10 (2B), U11.2 (1B)
H5: U2.13 (QB), U6.4 (1C), U6.9 (2A), U11.1 (1A)
H21: U12.3 (1Y), U13.5 (2A)
HBLANK: U11.3 (1Y), U13.2 (1A)
HC: U1.15 (RCO), U2.10 (ENT), U6.1 (1A)
HSYNC_N: U6.8 (2Y), U10.1 (1A)
LINE_END: U3.7 (ENP), U3.10 (ENT), U4.7 (ENP), U5.7 (ENP), U7.11 (G), U9.6 (3Y)
LINE_END_N: U2.9 (LOAD_N), U6.6 (1Y), U9.5 (3A)
SYNC: U10.3 (1Y), U10.4 (2A)
SYNC_N: J2.2 (SYNC_N), U14.5 (1Q)
SYNC_N_D: U10.6 (2Y), U14.2 (1D)
V0: U3.14 (QA), U7.6 (F), U12.10 (3B)
V1: U3.13 (QB), U7.5 (E), U12.9 (3A)
V2: U3.12 (QC), U7.4 (D), U8.4 (D), U12.5 (2B)
V3: U3.11 (QD), U9.3 (2A), U12.4 (2A)
V3_N: U8.5 (E), U9.4 (2Y)
V4: U4.14 (QA), U7.3 (C), U8.3 (C)
V5: U4.13 (QB), U7.2 (B), U8.2 (B), U11.5 (2B)
V8: U5.14 (QA), U7.1 (A), U8.1 (A), U11.4 (2A)
V10: U12.8 (3Y), U13.9 (3B)
V32: U12.6 (2Y), U13.8 (3A)
VBLANK: U11.6 (2Y), U13.3 (1B)
VC1: U3.15 (RCO), U4.10 (ENT)
VC2: U4.15 (RCO), U5.10 (ENT)
VCC: J1.1 (VCC), U1.1 (CLR_N), U1.7 (ENP), U1.9 (LOAD_N), U1.10 (ENT), U1.16 (VCC), U2.1 (CLR_N), U2.7 (ENP), U2.16 (VCC), U3.1 (CLR_N), U3.16 (VCC), U4.1 (CLR_N), U4.16 (VCC), U5.1 (CLR_N), U5.16 (VCC), U6.5 (1D), U6.14 (VCC), U7.12 (H), U7.14 (VCC), U8.6 (F), U8.11 (G), U8.12 (H), U8.14 (VCC), U9.14 (VCC), U10.5 (2B), U10.14 (VCC), U11.14 (VCC), U12.14 (VCC), U13.14 (VCC), U14.1 (1CLR_N), U14.4 (1PRE_N), U14.10 (2PRE_N), U14.13 (2CLR_N), U14.14 (VCC), X1.14 (VCC)
VIDEO: J2.1 (VIDEO), U14.9 (2Q)
VIDEO_D: U11.8 (3Y), U14.12 (2D)
VSYNC_N: U8.8 (Y), U10.2 (1B)
